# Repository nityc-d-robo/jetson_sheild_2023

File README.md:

# jetson_sheild_2023
Jetson sheild to use vl53l1x, bno055 and onboard CAN.
## KiCAD Version
KiCAD 7.0.7

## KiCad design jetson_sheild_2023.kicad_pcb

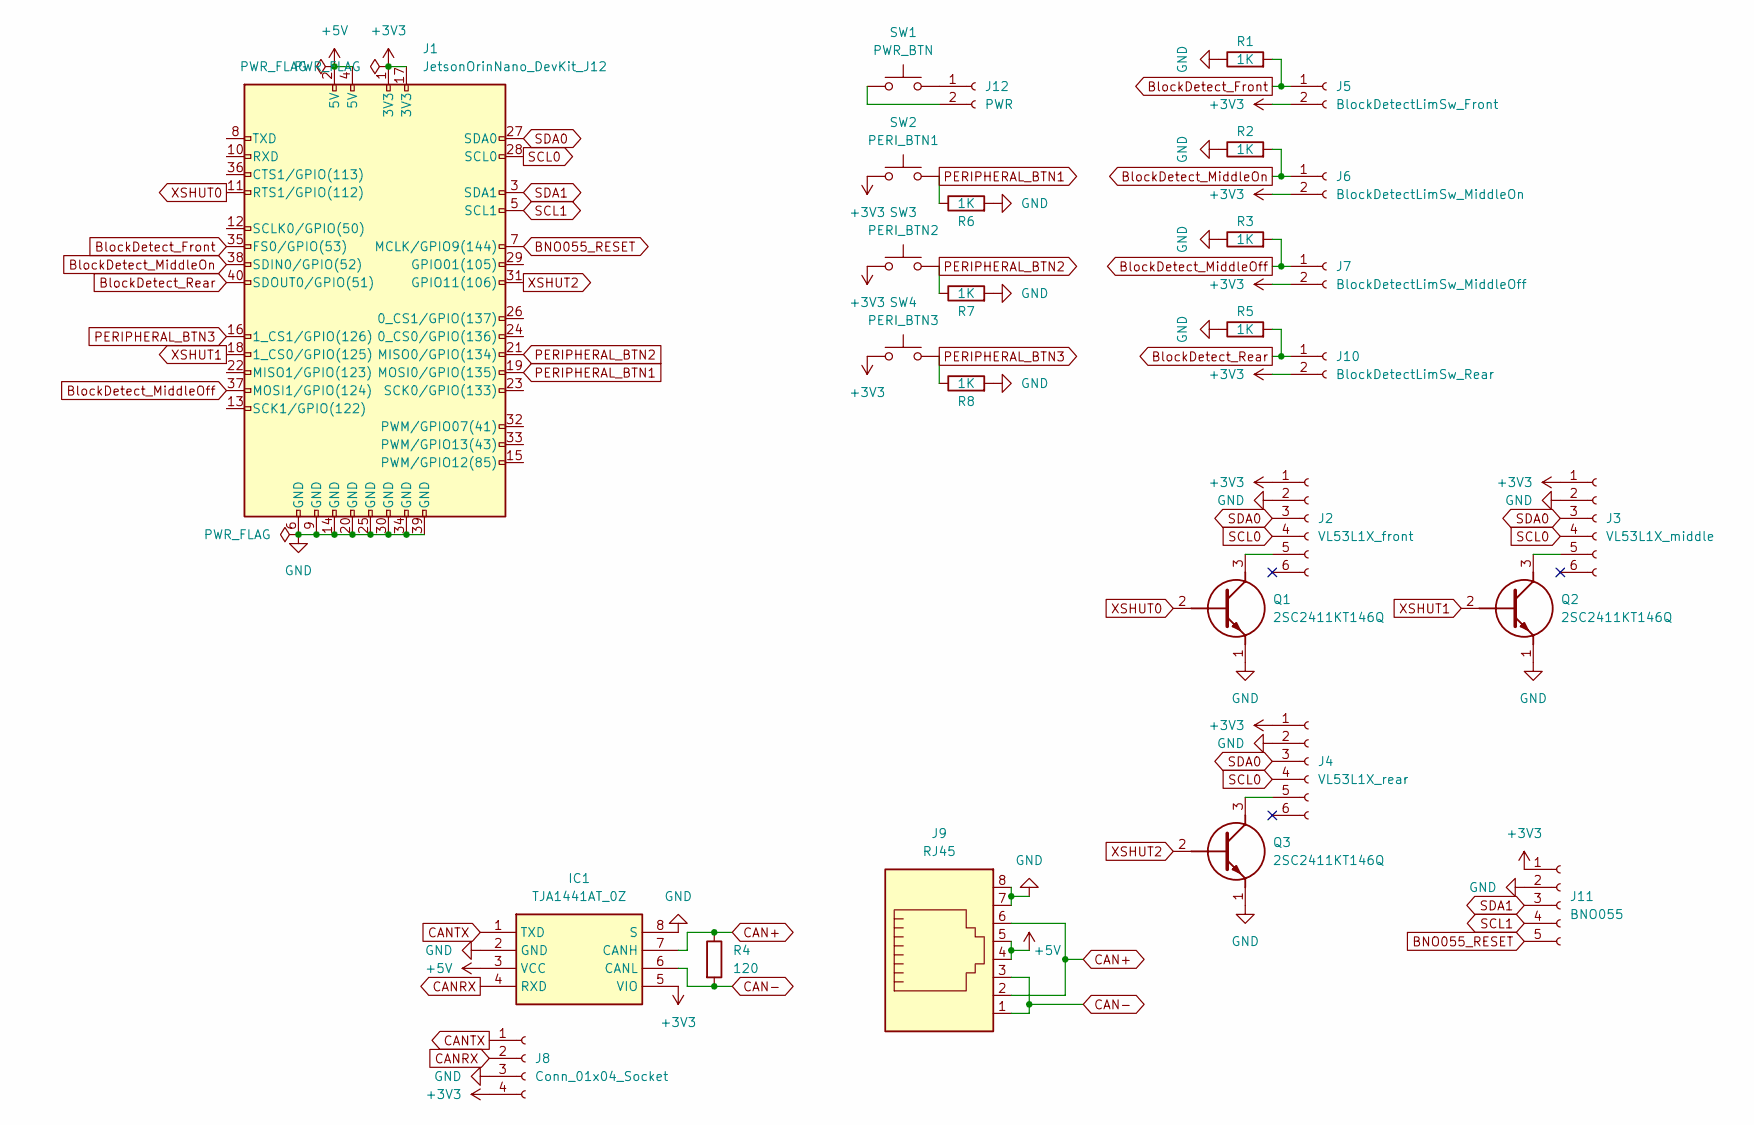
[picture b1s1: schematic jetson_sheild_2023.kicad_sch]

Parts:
IC1: TJA1441AT_0Z; SOIC-8_3.9x4.9mm_P1.27mm; Manufacturer_Part_Number TJA1441AT/0Z
J1: JetsonOrinNano_DevKit_J12; PinSocket_2x20_P2.54mm_Horizontal
J2: VL53L1X_front; JST_PH_S6B-PH-K_1x06_P2.00mm_Horizontal
J3: VL53L1X_middle; JST_PH_S6B-PH-K_1x06_P2.00mm_Horizontal
J4: VL53L1X_rear; JST_PH_S6B-PH-K_1x06_P2.00mm_Horizontal
J5: BlockDetectLimSw_Front; JST_XH_S2B-XH-A_1x02_P2.50mm_Horizontal
J6: BlockDetectLimSw_MiddleOn; JST_XH_S2B-XH-A_1x02_P2.50mm_Horizontal
J7: BlockDetectLimSw_MiddleOff; JST_XH_S2B-XH-A_1x02_P2.50mm_Horizontal
J8: Conn_01x04_Socket; JST_PH_S4B-PH-K_1x04_P2.00mm_Horizontal
J9: RJ45; RJ45_Amphenol_54602-x08_Horizontal
J10: BlockDetectLimSw_Rear; JST_XH_S2B-XH-A_1x02_P2.50mm_Horizontal
J11: BNO055; JST_PH_S5B-PH-K_1x05_P2.00mm_Horizontal
J12: PWR; JST_XH_B2B-XH-A_1x02_P2.50mm_Vertical
Q1, Q2, Q3: 2SC2411KT146Q; DTB123YKT146; Manufacturer_Part_Number 2SC2411KT146Q
R1, R2, R3, R5, R6, R7, R8: 1K; R_0603_1608Metric_Pad0.98x0.95mm_HandSolder
R4: 120; R_0603_1608Metric_Pad0.98x0.95mm_HandSolder
SW1: PWR_BTN; SW_SPST_PTS645
SW2: PERI_BTN1; SW_SPST_PTS645
SW3: PERI_BTN2; SW_SPST_PTS645
SW4: PERI_BTN3; SW_SPST_PTS645

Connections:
+3V3: IC1.5 (VIO), J1.1 (3V3), J1.17 (3V3), J2.1, J3.1, J4.1, J5.2, J6.2, J7.2, J8.4, J10.2, J11.1, SW2.1, SW3.1, SW4.1
+5V: IC1.3 (VCC), J1.2 (5V), J1.4 (5V), J9.4, J9.5
BNO055_RESET: J1.7 (MCLK/GPIO9(144)), J11.5
BlockDetect_Front: J1.35 (FS0/GPIO(53)), J5.1, R1.2
BlockDetect_MiddleOff: J1.37 (MOSI1/GPIO(124)), J7.1, R3.2
BlockDetect_MiddleOn: J1.38 (SDIN0/GPIO(52)), J6.1, R2.2
BlockDetect_Rear: J1.40 (SDOUT0/GPIO(51)), J10.1, R5.2
CAN+: IC1.7 (CANH), J9.2, J9.6, R4.1
CAN-: IC1.6 (CANL), J9.1, J9.3, R4.2
CANRX: IC1.4 (RXD), J8.2
CANTX: IC1.1 (TXD), J8.1
GND: IC1.2 (GND), IC1.8 (S), J1.6 (GND), J1.9 (GND), J1.14 (GND), J1.20 (GND), J1.25 (GND), J1.30 (GND), J1.34 (GND), J1.39 (GND), J2.2, J3.2, J4.2, J8.3, J9.7, J9.8, J11.2, Q1.1 (E), Q2.1 (E), Q3.1 (E), R1.1, R2.1, R3.1, R5.1, R6.2, R7.2, R8.2
unnamed: J2.5, Q1.3 (C)
unnamed: J3.5, Q2.3 (C)
unnamed: J4.5, Q3.3 (C)
unnamed: J12.1, SW1.2
unnamed: J12.2, SW1.1
PERIPHERAL_BTN1: J1.19 (MOSI0/GPIO(135)), R6.1, SW2.2
PERIPHERAL_BTN2: J1.21 (MISO0/GPIO(134)), R7.1, SW3.2
PERIPHERAL_BTN3: J1.16 (1_CS1/GPIO(126)), R8.1, SW4.2
SCL0: J1.28 (SCL0), J2.4, J3.4, J4.4
SCL1: J1.5 (SCL1), J11.4
SDA0: J1.27 (SDA0), J2.3, J3.3, J4.3
SDA1: J1.3 (SDA1), J11.3
XSHUT0: J1.11 (RTS1/GPIO(112)), Q1.2 (B)
XSHUT1: J1.18 (1_CS0/GPIO(125)), Q2.2 (B)
XSHUT2: J1.31 (GPIO11(106)), Q3.2 (B)

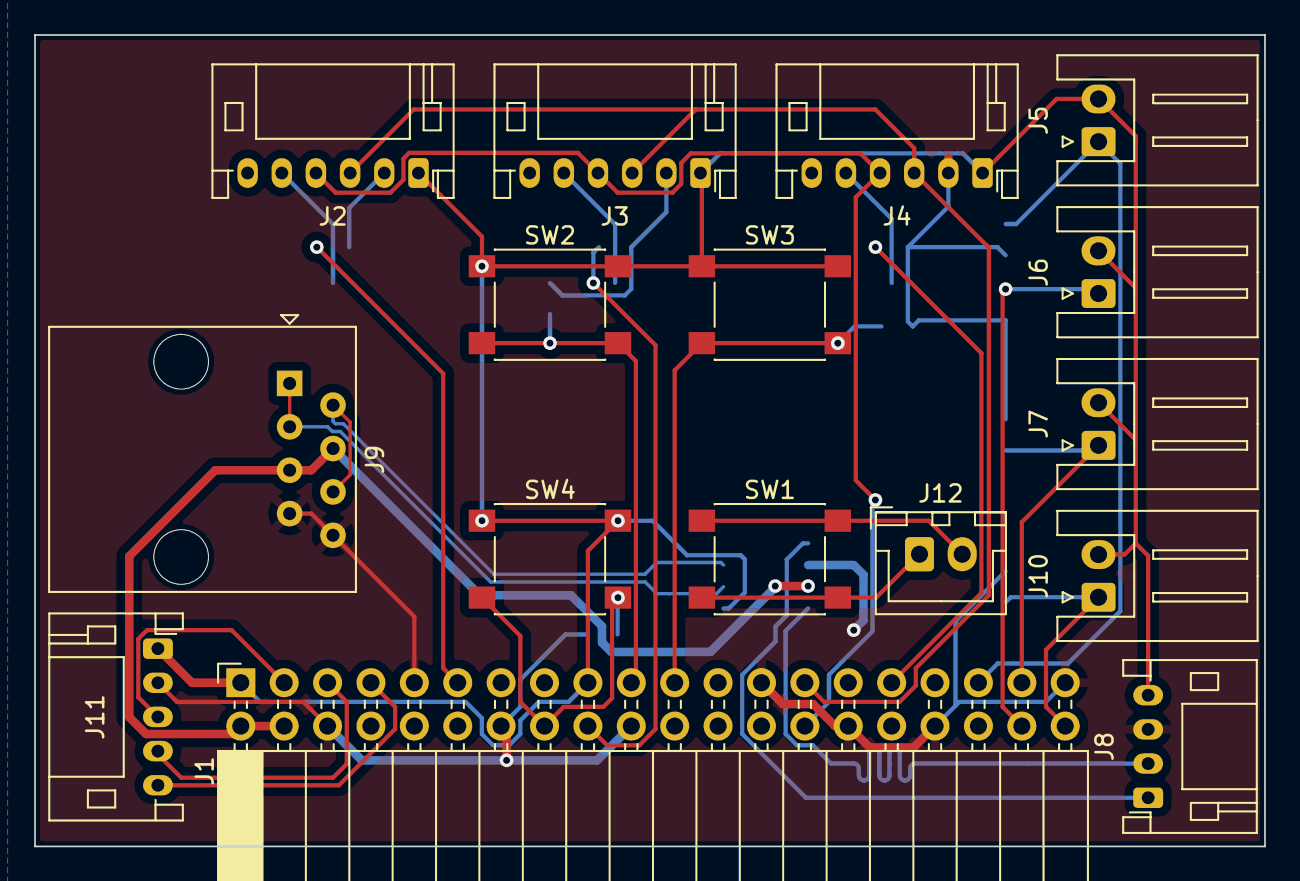
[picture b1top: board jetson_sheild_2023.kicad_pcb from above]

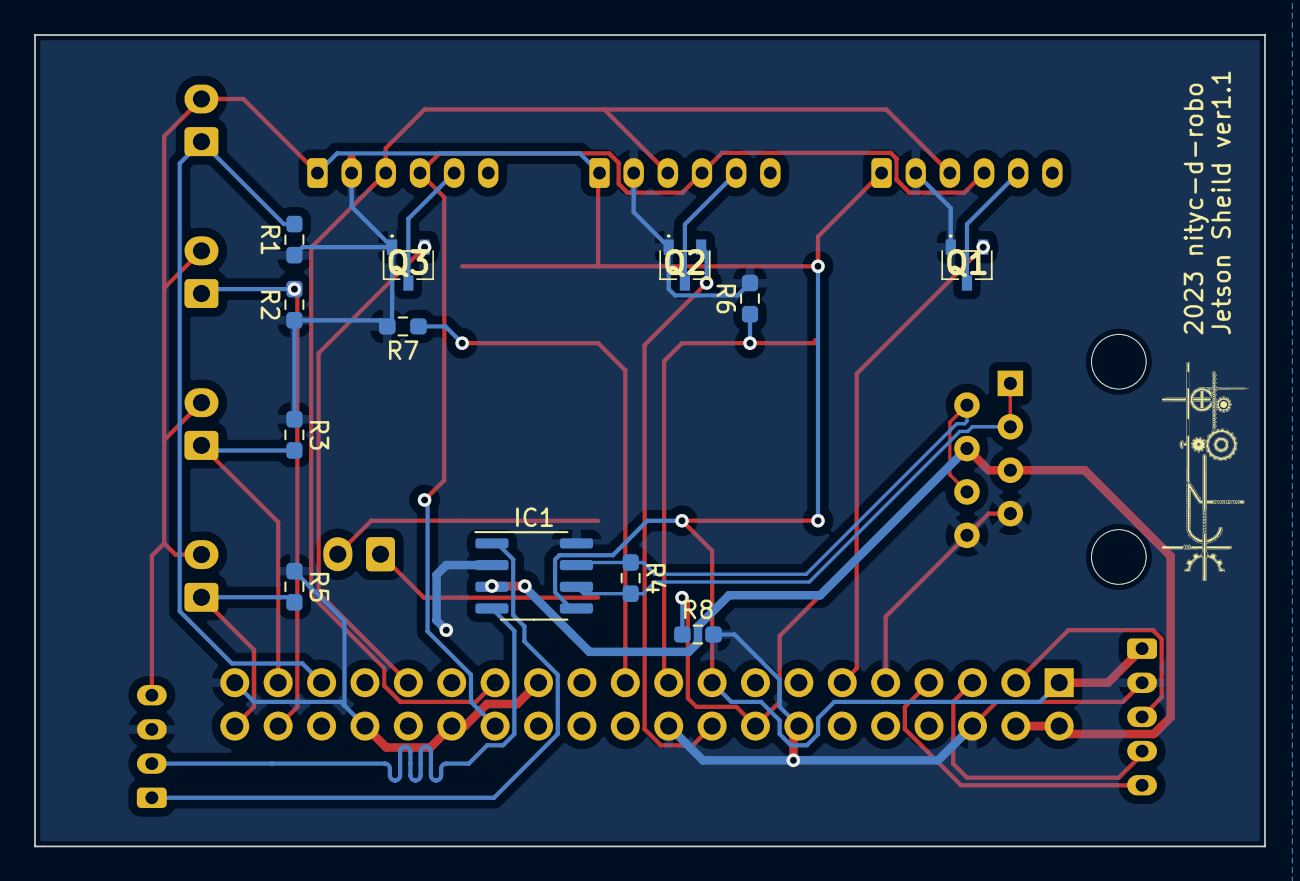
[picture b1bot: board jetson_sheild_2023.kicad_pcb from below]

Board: 2 copper layers, 72.0 x 47.5 mm, 28 parts (12 on the bottom side), 27 nets.

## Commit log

2023-10-04 ZHコネクタをPHコネクタに変更,電源ボタンと汎用ボタンを追加,バージョンとロゴを印字
